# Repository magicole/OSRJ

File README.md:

# OSRJ
Open Source Robotic Joint for use in robot arms and other robotics applications. This repository is broken into three main categories: Hardware, Software, and Documentation. Please see the README in each of those folders for more information about each component.

This repo contains submodules make sure you run the following commands:

```bash
git submodule init
git submodule update
```

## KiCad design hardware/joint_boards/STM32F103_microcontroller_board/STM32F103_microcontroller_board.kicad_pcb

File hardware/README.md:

# Open Source Robotic Joint Hardware

The hardware of OSRJ can be split into two categories: electrical and mechanical. Electrical hardware includes all circuit boards, power systems, and motors.
Mechanical hardware includes gearboxes, enclosures, and structrural components.

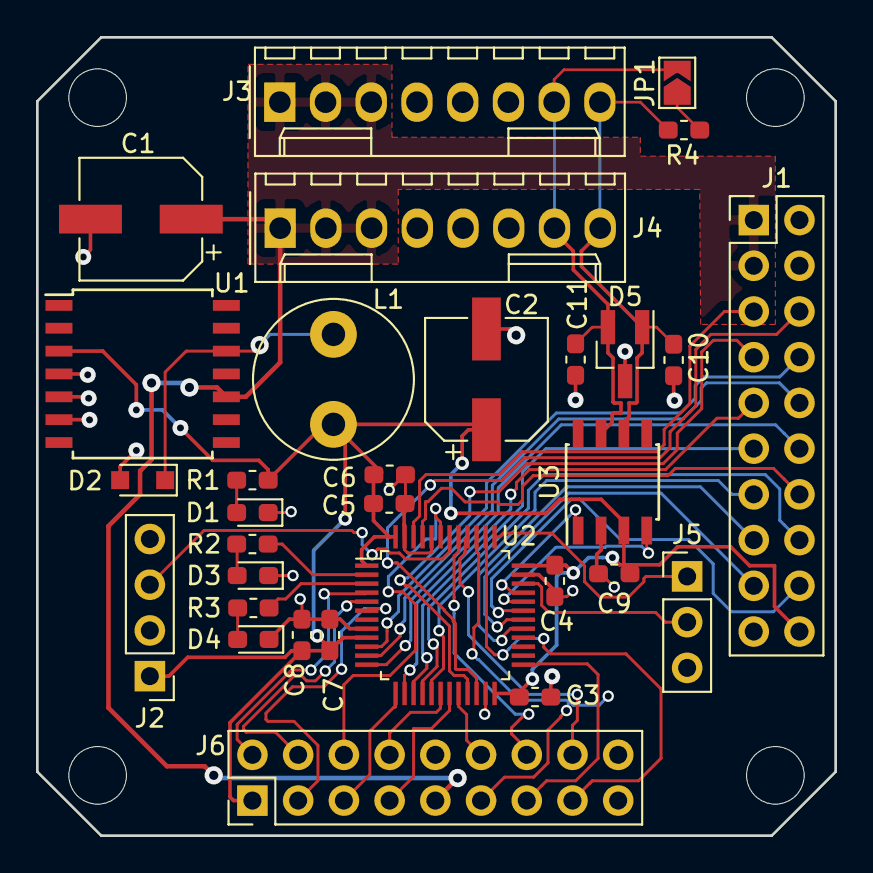
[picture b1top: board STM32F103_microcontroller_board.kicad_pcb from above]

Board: 2 copper layers, 44.4 x 44.4 mm, 31 parts (0 on the bottom side), 44 nets.

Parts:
C1: 22uF; CP_Elec_6.3x5.4
C2: 220uF; CP_Elec_6.3x5.4
C3, C4, C5, C9, C10, C11: 100nF; C_0603_1608Metric_Pad1.05x0.95mm_HandSolder
C6: 4.7uF; C_0603_1608Metric_Pad1.05x0.95mm_HandSolder
C7: 10nF; C_0603_1608Metric_Pad1.05x0.95mm_HandSolder
C8: 1uF; C_0603_1608Metric_Pad1.05x0.95mm_HandSolder
D1: RED LED; LED_0603_1608Metric_Pad1.05x0.95mm_HandSolder
D2: SR106; D_SOD-323_HandSoldering
D3: GRN LED; LED_0603_1608Metric_Pad1.05x0.95mm_HandSolder
D4: BLUE LED; LED_0603_1608Metric_Pad1.05x0.95mm_HandSolder
D5: ESDCAN24-2BLY; SOT-23_Handsoldering
J1: Conn_02x10_Odd_Even; PinHeader_2x10_P2.54mm_Vertical
J2: Conn_01x04; PinHeader_1x04_P2.54mm_Vertical
J3, J4: Conn_01x04; Molex_KK-254_AE-6410-08A_1x08_P2.54mm_Vertical
J5: Conn_01x03; PinHeader_1x03_P2.54mm_Vertical
J6: Conn_02x09_Counter_Clockwise; PinHeader_2x09_P2.54mm_Vertical
JP1: RtermJumper; SolderJumper-2_P1.3mm_Open_TrianglePad1.0x1.5mm
L1: 330uH; L_Radial_D8.7mm_P5.00mm_Fastron_07HCP
R1, R2: 68; R_0603_1608Metric_Pad1.05x0.95mm_HandSolder
R3: 33; R_0603_1608Metric_Pad1.05x0.95mm_HandSolder
R4: 120; R_0603_1608Metric_Pad1.05x0.95mm_HandSolder
U1: LM2574HVM-3.3; SOIC-14W_7.5x9.0mm_P1.27mm
U2: STM32F103CBTx; LQFP-48_7x7mm_P0.5mm
U3: SN65HVD232; SOIC-8_3.9x4.9mm_P1.27mm

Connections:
+3V3: C2.1, C3.1, C4.1, C5.1, C6.1, C7.1, C8.1, C9.1, J1.20, J2.1, J6.1, L1.2, R1.2, U1.3, U2.1, U2.9, U2.24, U2.36, U2.48, U3.3
/CAN+: C11.1, D5.2, J3.7, J4.7, JP1.2, U3.7
/CAN-: C10.2, D5.1, J3.8, J4.8, R4.1, U3.6
/CANRX: U2.32, U3.4
/CANTX: U2.33, U3.1
/Enable: J1.5, U2.46
/FWD_REV: J1.7, U2.21
/OSC_IN: J6.4, U2.5
/OSC_OUT: J6.3, U2.6
/PA3: J6.5, U2.13
/PA15: J6.15, U2.38
/PB0: J6.8, U2.18
/PB1: J6.7, U2.19
/PB2: J6.12, U2.20
/PB3: J6.11, U2.39
/PB4: J6.16, U2.40
/PB5: J6.14, U2.41
/PB7: J6.6, U2.43
/PB12: J6.13, U2.25
/PC15: J6.2, U2.4
/SWCLK: J5.1, U2.37
/SWDIO: J5.2, U2.34
/Speed_PWM: J1.6, U2.22
/U_driver: J1.15, U2.29
/U_encoder: J1.8, U2.10
/VIN: C1.1, J1.1, J1.3, J3.1, J3.2, J3.3, J4.1, J4.2, J4.3, J6.9, U1.10
/V_driver: J1.17, U2.30
/V_encoder: J1.10, U2.11
/W_driver: J1.18, U2.31
/W_encoder: J1.12, U2.12
/as5040_CLK: J1.11, U2.15
/as5040_CS: J1.9, U2.14
/as5040_DO: J1.16, U2.16
/as5040_LSB_PWM: J1.14, U2.45
/as5040_PROG: J1.13, U2.17
/local_encoder_pwm: J2.3, U2.42
GND: C1.2, C2.2, C3.2, C4.2, C5.2, C6.2, C7.2, C8.2, C9.2, C10.1, C11.2, D1.1, D2.2, D3.1, D4.1, D5.3, J1.2, J1.4, J1.19, J2.2, J2.4, J3.4, J3.5, J3.6, J4.4, J4.5, J4.6, J5.3, J6.10, J6.17, J6.18, U1.4, U1.5, U1.6, U2.8, U2.23, U2.35, U2.44, U2.47, U3.2
unnamed: D1.2, R1.1
unnamed: D2.1, L1.1, U1.12
unnamed: D3.2, R2.2
unnamed: D4.2, R3.1
unnamed: JP1.1, R4.2
unnamed: R2.1, U2.2
unnamed: R3.2, U2.3

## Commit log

2018-02-19 Set theme jekyll-theme-slate
2018-02-19 Initial github pages init
2018-02-19 initial scope post
2018-02-20 Add post table of contents to main page
2018-02-20 update theme to type on strap
2018-02-21 type on strap didnt work, changing to minimal mistakes
2018-02-22 added prior work post
2018-02-25 updated categories for better organization
2018-02-28 testing how jenkins works
2018-06-05 Updated repo organization, added README throughout
2018-10-17 checking in so things are recorded
2018-10-25 reorganized the directory structure because kicad can only do one board per project
2018-11-06 version 1 of MCU schematic
2018-11-11 footprints associated and schematic finalized. Most components have sources
2018-11-12 board layed out after 6 hours
2018-11-17 basic schematic setup for driver board
2019-07-24 set up code and added LED library
